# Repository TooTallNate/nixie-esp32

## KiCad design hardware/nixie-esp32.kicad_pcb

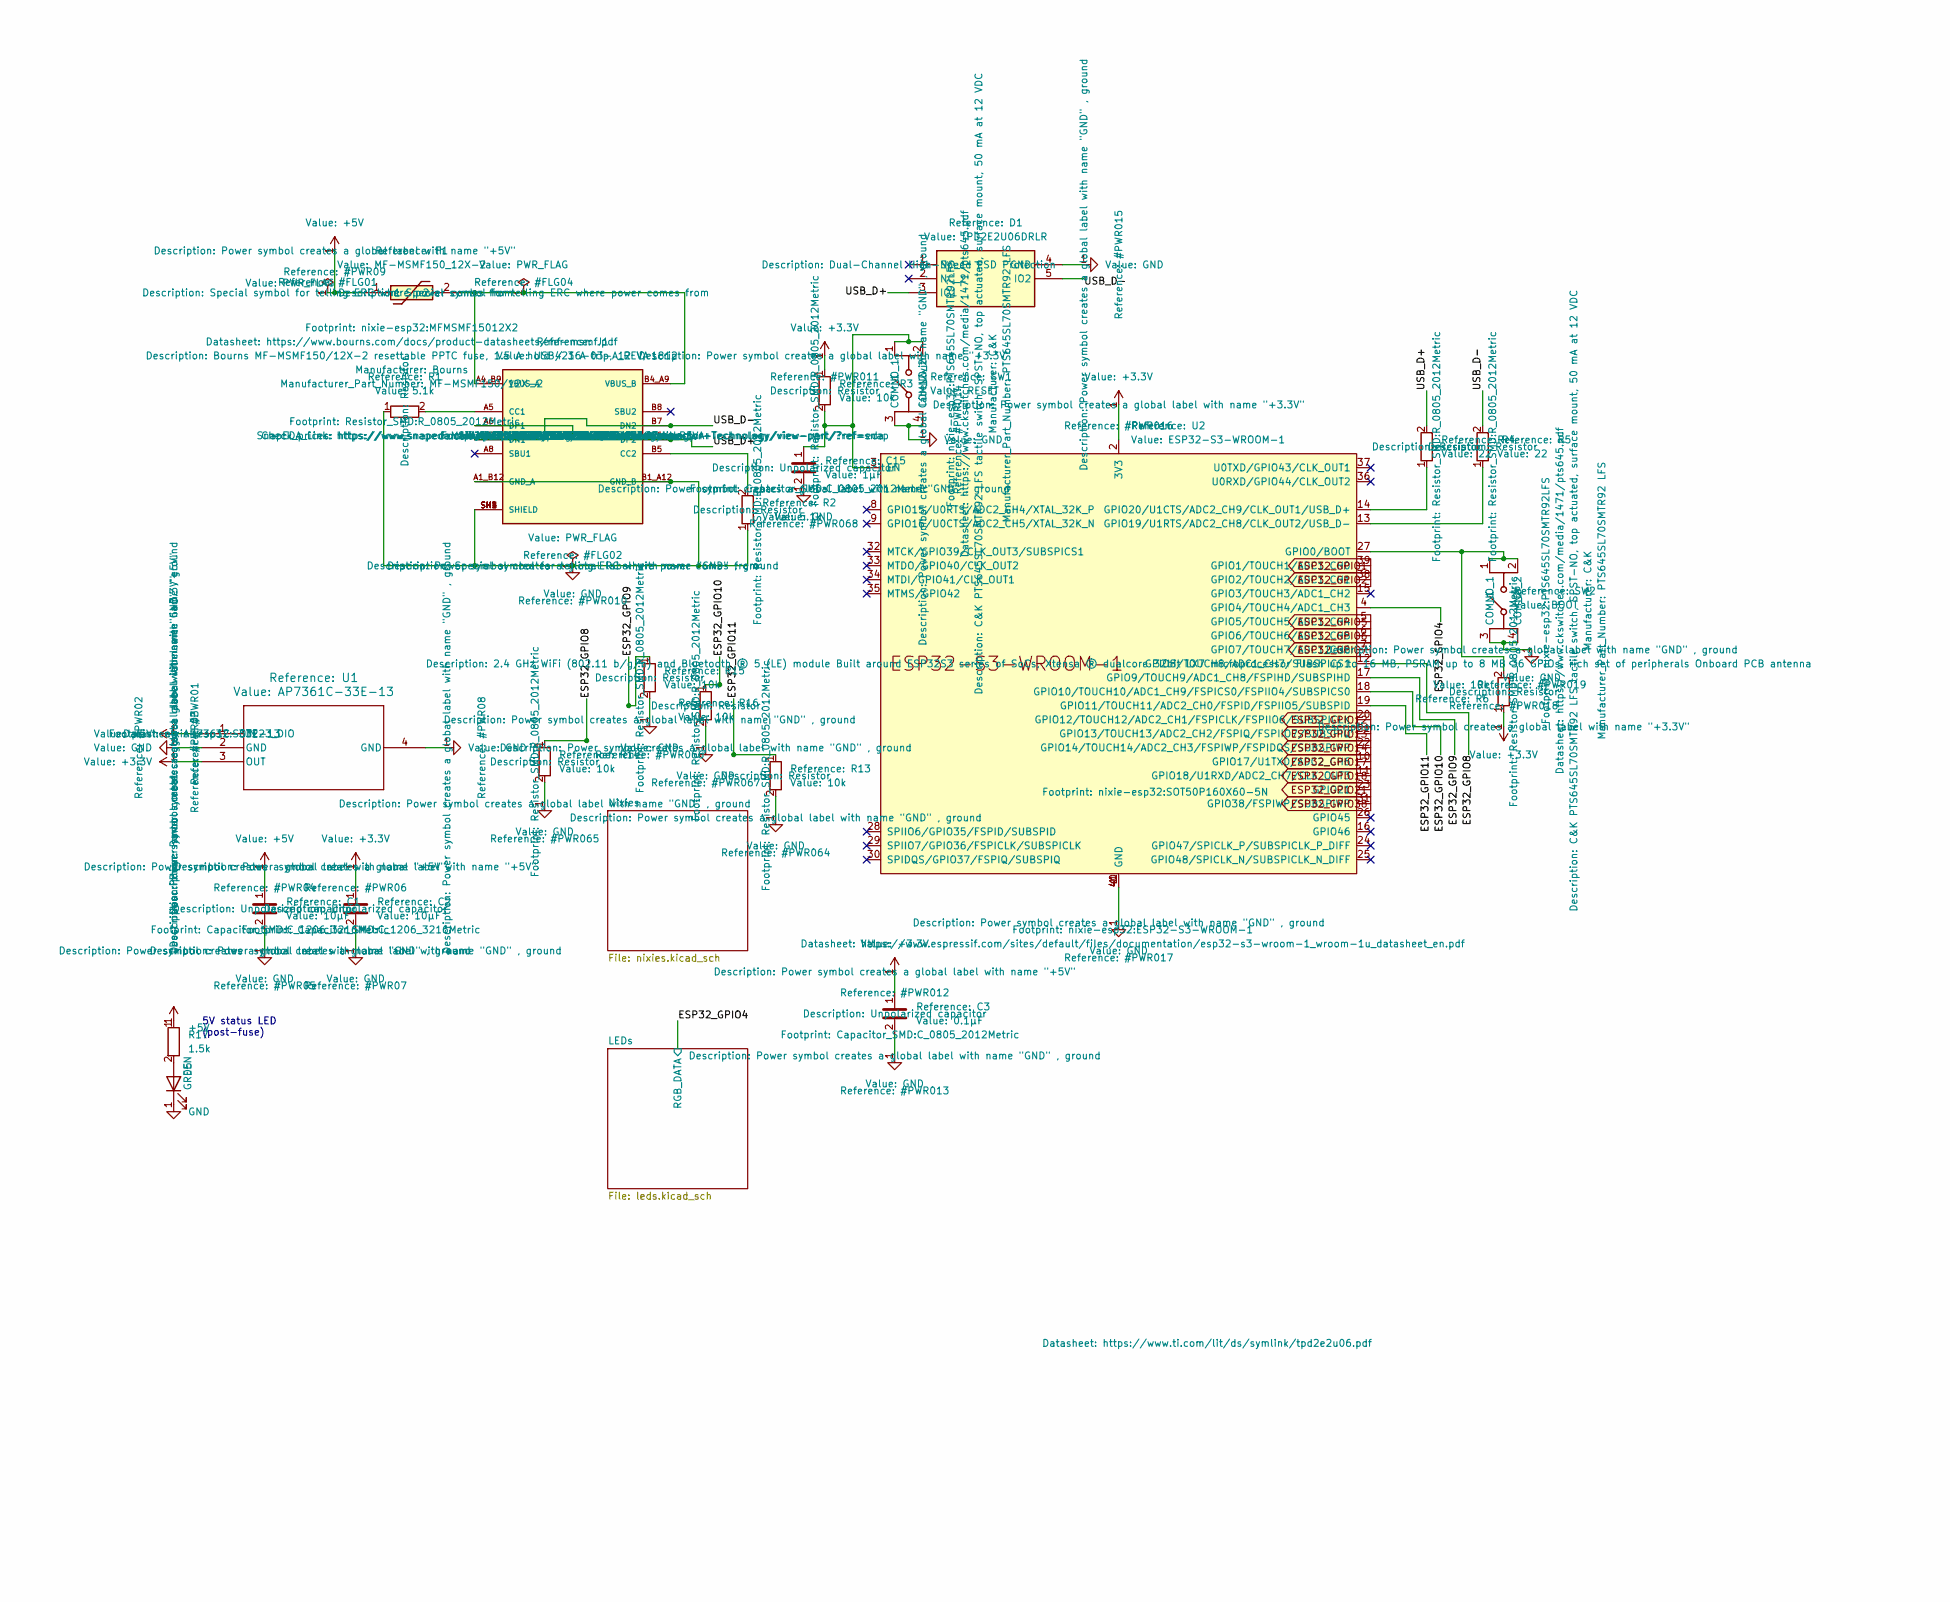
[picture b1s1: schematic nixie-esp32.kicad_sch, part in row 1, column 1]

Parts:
C1, C2: 10µF; C_1206_3216Metric
C3: 0.1µF; C_0805_2012Metric
C15: 1µF; C_0805_2012Metric
D1: TPD2E2U06DRLR; SOT50P160X60-5N; Mouser Part Number 595-TPD2E2U06DRLR
D5: GREEN; LED_0805_2012Metric
F1: MF-MSMF150_12X-2; MFMSMF15012X2; Manufacturer_Part_Number MF-MSMF150/12X-2
J1: USB4216-03-A_REVA; GCT_USB4216-03-A_REVA; PARTREV A
R1, R2: 5.1k; R_0805_2012Metric
R3, R6, R13, R14, R15, R16: 10k; R_0805_2012Metric
R4, R5: 22; R_0805_2012Metric
R17: 1.5k; R_0805_2012Metric
SW1: RESET; PTS645SL70SMTR92LFS; Manufacturer_Part_Number PTS645SL70SMTR92 LFS
SW2: BOOT; PTS645SL70SMTR92LFS; Manufacturer_Part_Number PTS645SL70SMTR92 LFS
U1: AP7361C-33E-13; SOT223_DIO
U2: ESP32-S3-WROOM-1

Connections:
+3.3V: C2.1, C3.1, R3.1, R6.1, U1.3 (OUT), U2.2 (3V3); also elsewhere on the board
+5V: C1.1, F1.1, R17.1, U1.1 (IN); also elsewhere on the board
/ESP32_GPIO4: U2.4 (GPIO4/TOUCH4/ADC1_CH3); also elsewhere on the board
/ESP32_GPIO8: R14.1, U2.12 (GPIO8/TOUCH8/ADC1_CH7/SUBSPICS1)
/ESP32_GPIO9: R15.1, U2.17 (GPIO9/TOUCH9/ADC1_CH8/FSPIHD/SUBSPIHD)
/ESP32_GPIO10: R16.1, U2.18 (GPIO10/TOUCH10/ADC1_CH9/FSPICS0/FSPIIO4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)
/ESP32_GPIO11: R13.1, U2.19 (GPIO11/TOUCH11/ADC2_CH0/FSPID/FSPIIO5/S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)
/USB_D+: D1.3 (IO1), J1.A6 (DP1), J1.B6 (DP2), R4.2
/USB_D-: D1.5 (IO2), J1.A7 (DN1), J1.B7 (DN2), R5.2
ESP32_GPIO1: U2.39 (GPIO1/TOUCH1/ADC1_CH0); also elsewhere on the board
ESP32_GPIO2: U2.38 (GPIO2/TOUCH2/ADC1_CH1); also elsewhere on the board
ESP32_GPIO5: U2.5 (GPIO5/TOUCH5/ADC1_CH4); also elsewhere on the board
ESP32_GPIO6: U2.6 (GPIO6/TOUCH6/ADC1_CH5); also elsewhere on the board
ESP32_GPIO7: U2.7 (GPIO7/TOUCH7/ADC1_CH6); also elsewhere on the board
ESP32_GPIO12: U2.20 (GPIO12/TOUCH12/ADC2_CH1/FSPICLK/FSPIIO6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); also elsewhere on the board
ESP32_GPIO13: U2.21 (GPIO13/TOUCH13/ADC2_CH2/FSPIQ/FSPIIO7/S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); also elsewhere on the board
ESP32_GPIO14: U2.22 (GPIO14/TOUCH14/ADC2_CH3/FSPIWP/FSPIDQS/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); also elsewhere on the board
ESP32_GPIO17: U2.10 (GPIO17/U1TXD/ADC2_CH6); also elsewhere on the board
ESP32_GPIO18: U2.11 (GPIO18/U1RXD/ADC2_CH7/CLK_OUT3); also elsewhere on the board
ESP32_GPIO21: U2.23 (GPIO21); also elsewhere on the board
ESP32_GPIO38: U2.31 (GPIO38/FSPIWP/SUBSPIWP); also elsewhere on the board
GND: C1.2, C2.2, C3.2, C15.2, D1.4 (GND), D5.1 (K), J1.A1_B12 (GND_A), J1.B1_A12 (GND_B), J1.SH1 (SHIELD), J1.SH2 (SHIELD), J1.SH3 (SHIELD), J1.SH4 (SHIELD), R1.1, R2.1, R13.2, R14.2, R15.2, R16.2, SW1.3 (COM_1), SW1.4 (COM_2), SW2.3 (COM_1), SW2.4 (COM_2), U1.2 (GND), U1.4 (GND), U2.1 (GND), U2.40 (GND), U2.41 (GND); also elsewhere on the board
unnamed: D5.2 (A), R17.2
unnamed: J1.A5 (CC1), R1.2
unnamed: J1.B5 (CC2), R2.2
unnamed: F1.2, J1.A4_B9 (VBUS_A), J1.B4_A9 (VBUS_B)
unnamed: C15.1, R3.2, SW1.1 (NO_1), SW1.2 (NO_2), U2.3 (EN)
unnamed: R6.2, SW2.1 (NO_1), SW2.2 (NO_2), U2.27 (GPIO0/BOOT)
unnamed: R5.1, U2.13 (GPIO19/U1RTS/ADC2_CH8/CLK_OUT2/USB_D-)
unnamed: R4.1, U2.14 (GPIO20/U1CTS/ADC2_CH9/CLK_OUT1/USB_D+)

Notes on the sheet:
5V status LED (post-fuse)

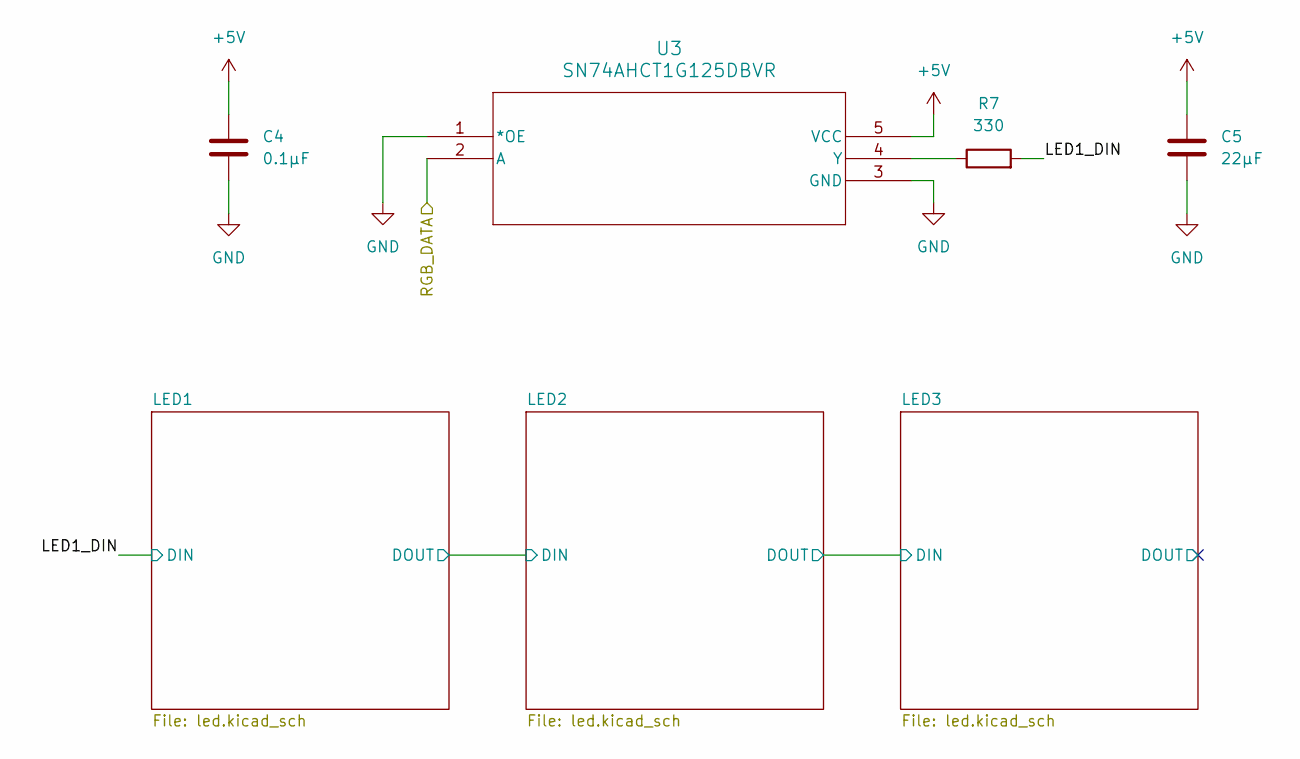
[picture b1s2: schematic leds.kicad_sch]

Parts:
C4: 0.1µF; C_0805_2012Metric
C5: 22µF; C_1206_3216Metric
R7: 330; R_0805_2012Metric
U3: SN74AHCT1G125DBVR; DBV5

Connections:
+5V: C4.1, C5.1, U3.5 (VCC); also elsewhere on the board
/ESP32_GPIO4: U3.2 (A); also elsewhere on the board
/LEDs/LED1_DIN: R7.2; also elsewhere on the board
GND: C4.2, C5.2, U3.1 (*OE), U3.3 (GND); also elsewhere on the board
unnamed: R7.1, U3.4 (Y)

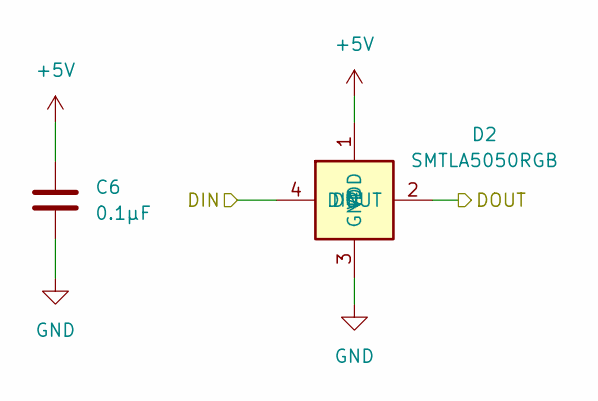
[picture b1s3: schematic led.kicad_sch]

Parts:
C6: 0.1µF; C_0805_2012Metric
D2: SMTLA5050RGB; Manufacturer_Part_Number SMTLA5050RGB

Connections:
+5V: C6.1, D2.1 (VDD); also elsewhere on the board
/LEDs/LED1/DOUT: D2.2 (DOUT); also elsewhere on the board
/LEDs/LED1_DIN: D2.4 (DIN); also elsewhere on the board
GND: C6.2, D2.3 (GND); also elsewhere on the board

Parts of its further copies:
C7, C8: 0.1µF; C_0805_2012Metric
D3, D4: SMTLA5050RGB; Manufacturer_Part_Number SMTLA5050RGB

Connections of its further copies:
+5V: C7.1, C8.1, D3.1 (VDD), D4.1 (VDD); also elsewhere on the board
/LEDs/LED1/DOUT: D3.4 (DIN); also elsewhere on the board
/LEDs/LED2/DOUT: D3.2 (DOUT), D4.4 (DIN)
/LEDs/LED3/DOUT: D4.2 (DOUT)
GND: C7.2, C8.2, D3.3 (GND), D4.3 (GND); also elsewhere on the board

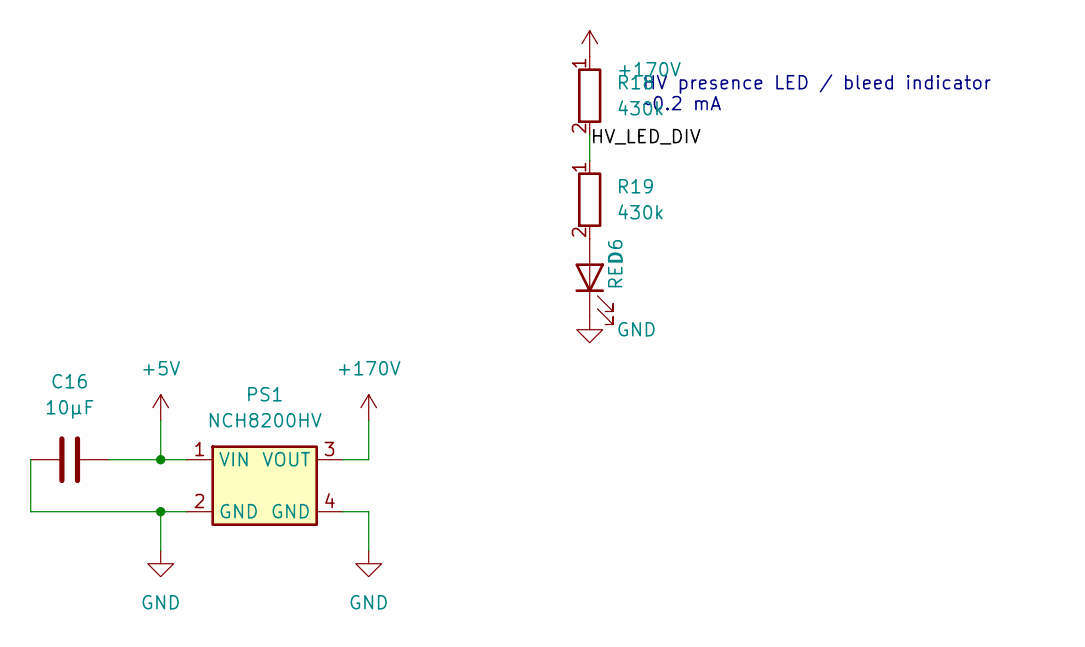
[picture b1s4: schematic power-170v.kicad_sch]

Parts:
C16: 10µF; C_1206_3216Metric
D6: RED; LED_0805_2012Metric
PS1: NCH8200HV
R18, R19: 430k; R_0805_2012Metric

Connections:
+5V: C16.1, PS1.1 (VIN); also elsewhere on the board
+170V: PS1.3 (VOUT), R18.1; also elsewhere on the board
/Nixies/Power170v/HV_LED_DIV: R18.2, R19.1
GND: C16.2, D6.1 (K), PS1.2 (GND), PS1.4 (GND); also elsewhere on the board
unnamed: D6.2 (A), R19.2

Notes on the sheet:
HV presence LED / bleed indicator ~0.2 mA

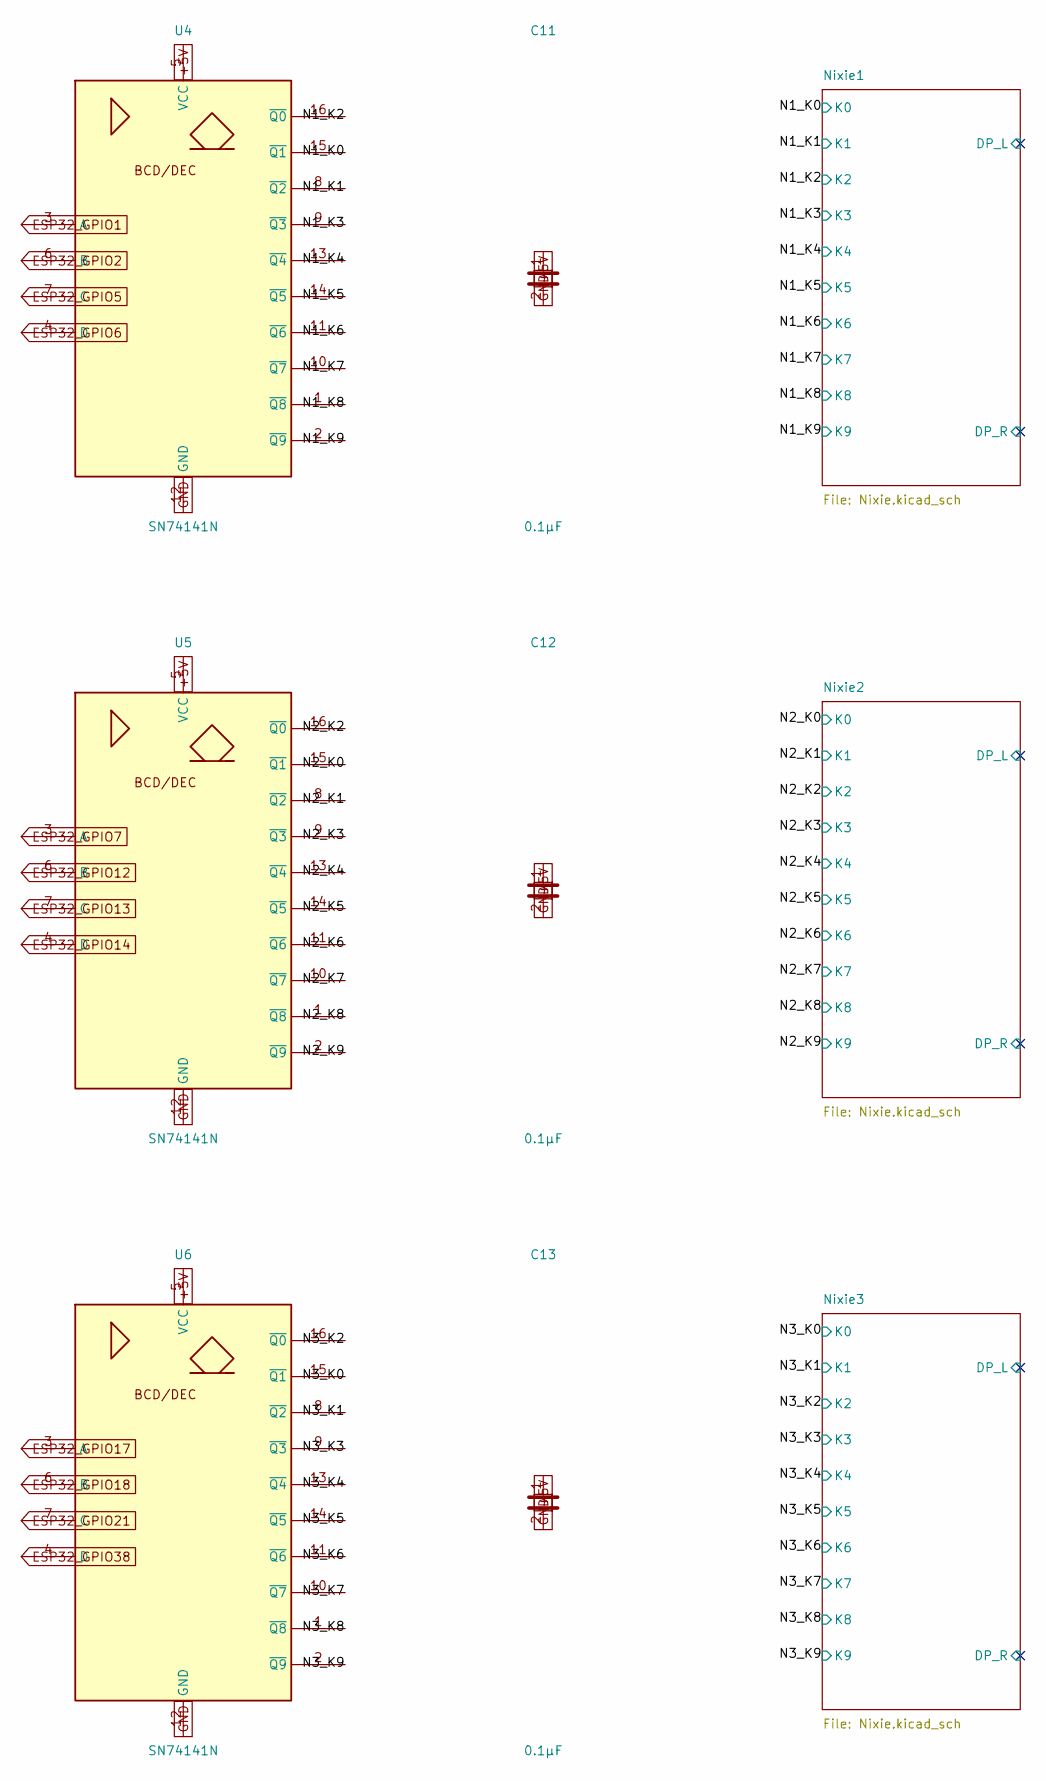
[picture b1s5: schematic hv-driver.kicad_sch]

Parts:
C11, C12, C13: 0.1µF; C_0805_2012Metric
U4, U5, U6: SN74141N; DIP-16_W7.62mm

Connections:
+5V: C11.1, C12.1, C13.1, U4.5 (VCC), U5.5 (VCC), U6.5 (VCC); also elsewhere on the board
/Nixies/HvDriver/N1_K0: U4.15 (~Q1); also elsewhere on the board
/Nixies/HvDriver/N1_K1: U4.8 (~Q2); also elsewhere on the board
/Nixies/HvDriver/N1_K2: U4.16 (~Q0); also elsewhere on the board
/Nixies/HvDriver/N1_K3: U4.9 (~Q3); also elsewhere on the board
/Nixies/HvDriver/N1_K4: U4.13 (~Q4); also elsewhere on the board
/Nixies/HvDriver/N1_K5: U4.14 (~Q5); also elsewhere on the board
/Nixies/HvDriver/N1_K6: U4.11 (~Q6); also elsewhere on the board
/Nixies/HvDriver/N1_K7: U4.10 (~Q7); also elsewhere on the board
/Nixies/HvDriver/N1_K8: U4.1 (~Q8); also elsewhere on the board
/Nixies/HvDriver/N1_K9: U4.2 (~Q9); also elsewhere on the board
/Nixies/HvDriver/N2_K0: U5.15 (~Q1); also elsewhere on the board
/Nixies/HvDriver/N2_K1: U5.8 (~Q2); also elsewhere on the board
/Nixies/HvDriver/N2_K2: U5.16 (~Q0); also elsewhere on the board
/Nixies/HvDriver/N2_K3: U5.9 (~Q3); also elsewhere on the board
/Nixies/HvDriver/N2_K4: U5.13 (~Q4); also elsewhere on the board
/Nixies/HvDriver/N2_K5: U5.14 (~Q5); also elsewhere on the board
/Nixies/HvDriver/N2_K6: U5.11 (~Q6); also elsewhere on the board
/Nixies/HvDriver/N2_K7: U5.10 (~Q7); also elsewhere on the board
/Nixies/HvDriver/N2_K8: U5.1 (~Q8); also elsewhere on the board
/Nixies/HvDriver/N2_K9: U5.2 (~Q9); also elsewhere on the board
/Nixies/HvDriver/N3_K0: U6.15 (~Q1); also elsewhere on the board
/Nixies/HvDriver/N3_K1: U6.8 (~Q2); also elsewhere on the board
/Nixies/HvDriver/N3_K2: U6.16 (~Q0); also elsewhere on the board
/Nixies/HvDriver/N3_K3: U6.9 (~Q3); also elsewhere on the board
/Nixies/HvDriver/N3_K4: U6.13 (~Q4); also elsewhere on the board
/Nixies/HvDriver/N3_K5: U6.14 (~Q5); also elsewhere on the board
/Nixies/HvDriver/N3_K6: U6.11 (~Q6); also elsewhere on the board
/Nixies/HvDriver/N3_K7: U6.10 (~Q7); also elsewhere on the board
/Nixies/HvDriver/N3_K8: U6.1 (~Q8); also elsewhere on the board
/Nixies/HvDriver/N3_K9: U6.2 (~Q9); also elsewhere on the board
ESP32_GPIO1: U4.3 (A); also elsewhere on the board
ESP32_GPIO2: U4.6 (B); also elsewhere on the board
ESP32_GPIO5: U4.7 (C); also elsewhere on the board
ESP32_GPIO6: U4.4 (D); also elsewhere on the board
ESP32_GPIO7: U5.3 (A); also elsewhere on the board
ESP32_GPIO12: U5.6 (B); also elsewhere on the board
ESP32_GPIO13: U5.7 (C); also elsewhere on the board
ESP32_GPIO14: U5.4 (D); also elsewhere on the board
ESP32_GPIO17: U6.3 (A); also elsewhere on the board
ESP32_GPIO18: U6.6 (B); also elsewhere on the board
ESP32_GPIO21: U6.7 (C); also elsewhere on the board
ESP32_GPIO38: U6.4 (D); also elsewhere on the board
GND: C11.2, C12.2, C13.2, U4.12 (GND), U5.12 (GND), U6.12 (GND); also elsewhere on the board

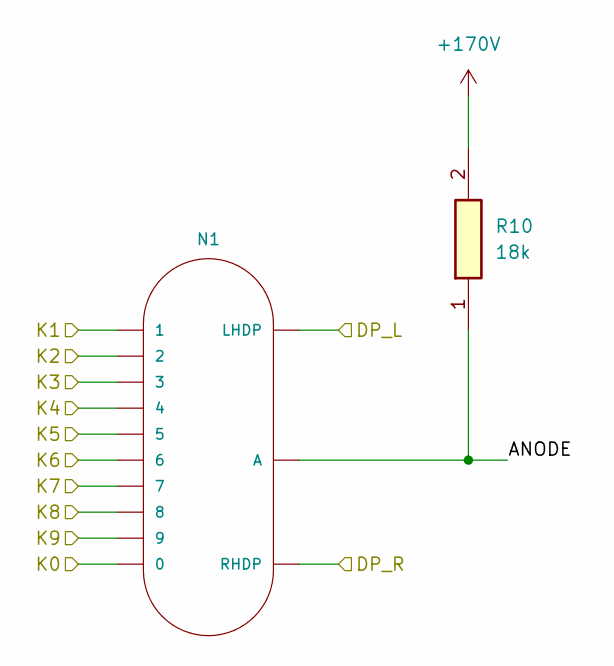
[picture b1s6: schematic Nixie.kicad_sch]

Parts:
N1: IN-14; nixies-us-IN-14
R10: 18k; RESC3116X65N; Tolerance 1%; Voltage_Rating 200 V; Manufacturer_Part_Number CRGH1206F18K

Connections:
+170V: R10.2; also elsewhere on the board
/Nixies/HvDriver/N1_K0: N1.0; also elsewhere on the board
/Nixies/HvDriver/N1_K1: N1.1; also elsewhere on the board
/Nixies/HvDriver/N1_K2: N1.2; also elsewhere on the board
/Nixies/HvDriver/N1_K3: N1.3; also elsewhere on the board
/Nixies/HvDriver/N1_K4: N1.4; also elsewhere on the board
/Nixies/HvDriver/N1_K5: N1.5; also elsewhere on the board
/Nixies/HvDriver/N1_K6: N1.6; also elsewhere on the board
/Nixies/HvDriver/N1_K7: N1.7; also elsewhere on the board
/Nixies/HvDriver/N1_K8: N1.8; also elsewhere on the board
/Nixies/HvDriver/N1_K9: N1.9; also elsewhere on the board
/Nixies/HvDriver/Nixie1/ANODE: N1.A, R10.1

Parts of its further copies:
N2, N3: IN-14; nixies-us-IN-14
R11, R12: 18k; RESC3116X65N; Tolerance 1%; Voltage_Rating 200 V; Manufacturer_Part_Number CRGH1206F18K

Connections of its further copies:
+170V: R11.2, R12.2; also elsewhere on the board
/Nixies/HvDriver/N2_K0: N2.0; also elsewhere on the board
/Nixies/HvDriver/N2_K1: N2.1; also elsewhere on the board
/Nixies/HvDriver/N2_K2: N2.2; also elsewhere on the board
/Nixies/HvDriver/N2_K3: N2.3; also elsewhere on the board
/Nixies/HvDriver/N2_K4: N2.4; also elsewhere on the board
/Nixies/HvDriver/N2_K5: N2.5; also elsewhere on the board
/Nixies/HvDriver/N2_K6: N2.6; also elsewhere on the board
/Nixies/HvDriver/N2_K7: N2.7; also elsewhere on the board
/Nixies/HvDriver/N2_K8: N2.8; also elsewhere on the board
/Nixies/HvDriver/N2_K9: N2.9; also elsewhere on the board
/Nixies/HvDriver/N3_K0: N3.0; also elsewhere on the board
/Nixies/HvDriver/N3_K1: N3.1; also elsewhere on the board
/Nixies/HvDriver/N3_K2: N3.2; also elsewhere on the board
/Nixies/HvDriver/N3_K3: N3.3; also elsewhere on the board
/Nixies/HvDriver/N3_K4: N3.4; also elsewhere on the board
/Nixies/HvDriver/N3_K5: N3.5; also elsewhere on the board
/Nixies/HvDriver/N3_K6: N3.6; also elsewhere on the board
/Nixies/HvDriver/N3_K7: N3.7; also elsewhere on the board
/Nixies/HvDriver/N3_K8: N3.8; also elsewhere on the board
/Nixies/HvDriver/N3_K9: N3.9; also elsewhere on the board
/Nixies/HvDriver/Nixie2/ANODE: N2.A, R11.1
/Nixies/HvDriver/Nixie3/ANODE: N3.A, R12.1

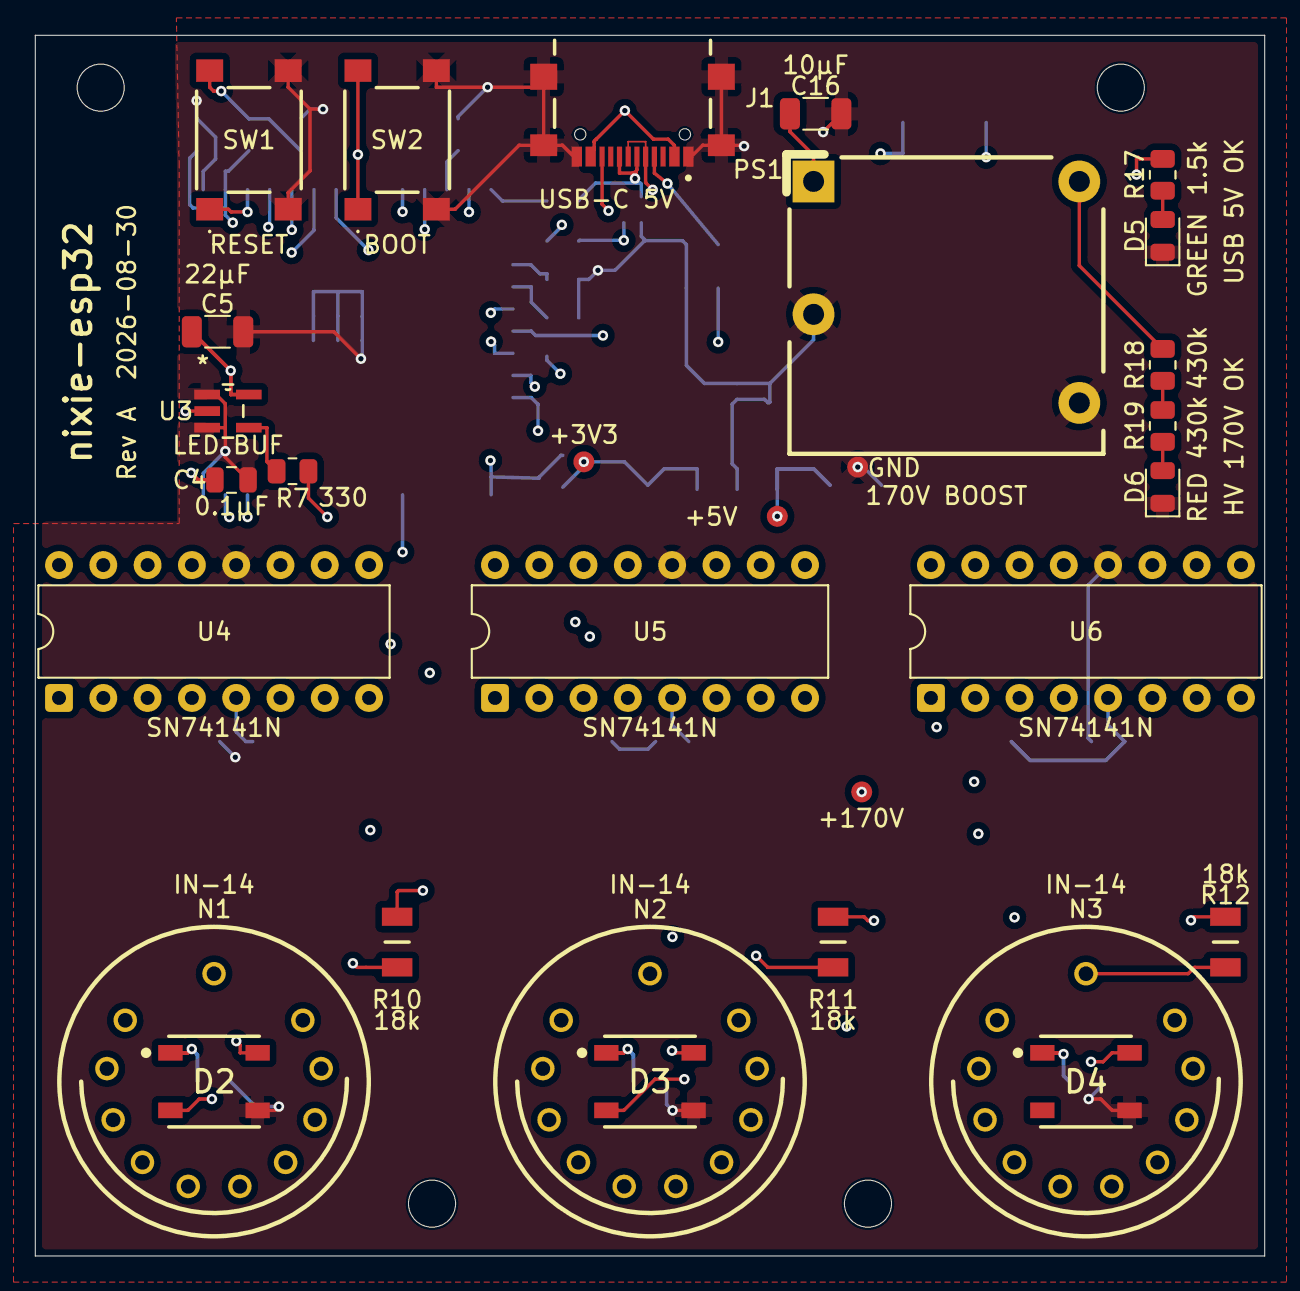
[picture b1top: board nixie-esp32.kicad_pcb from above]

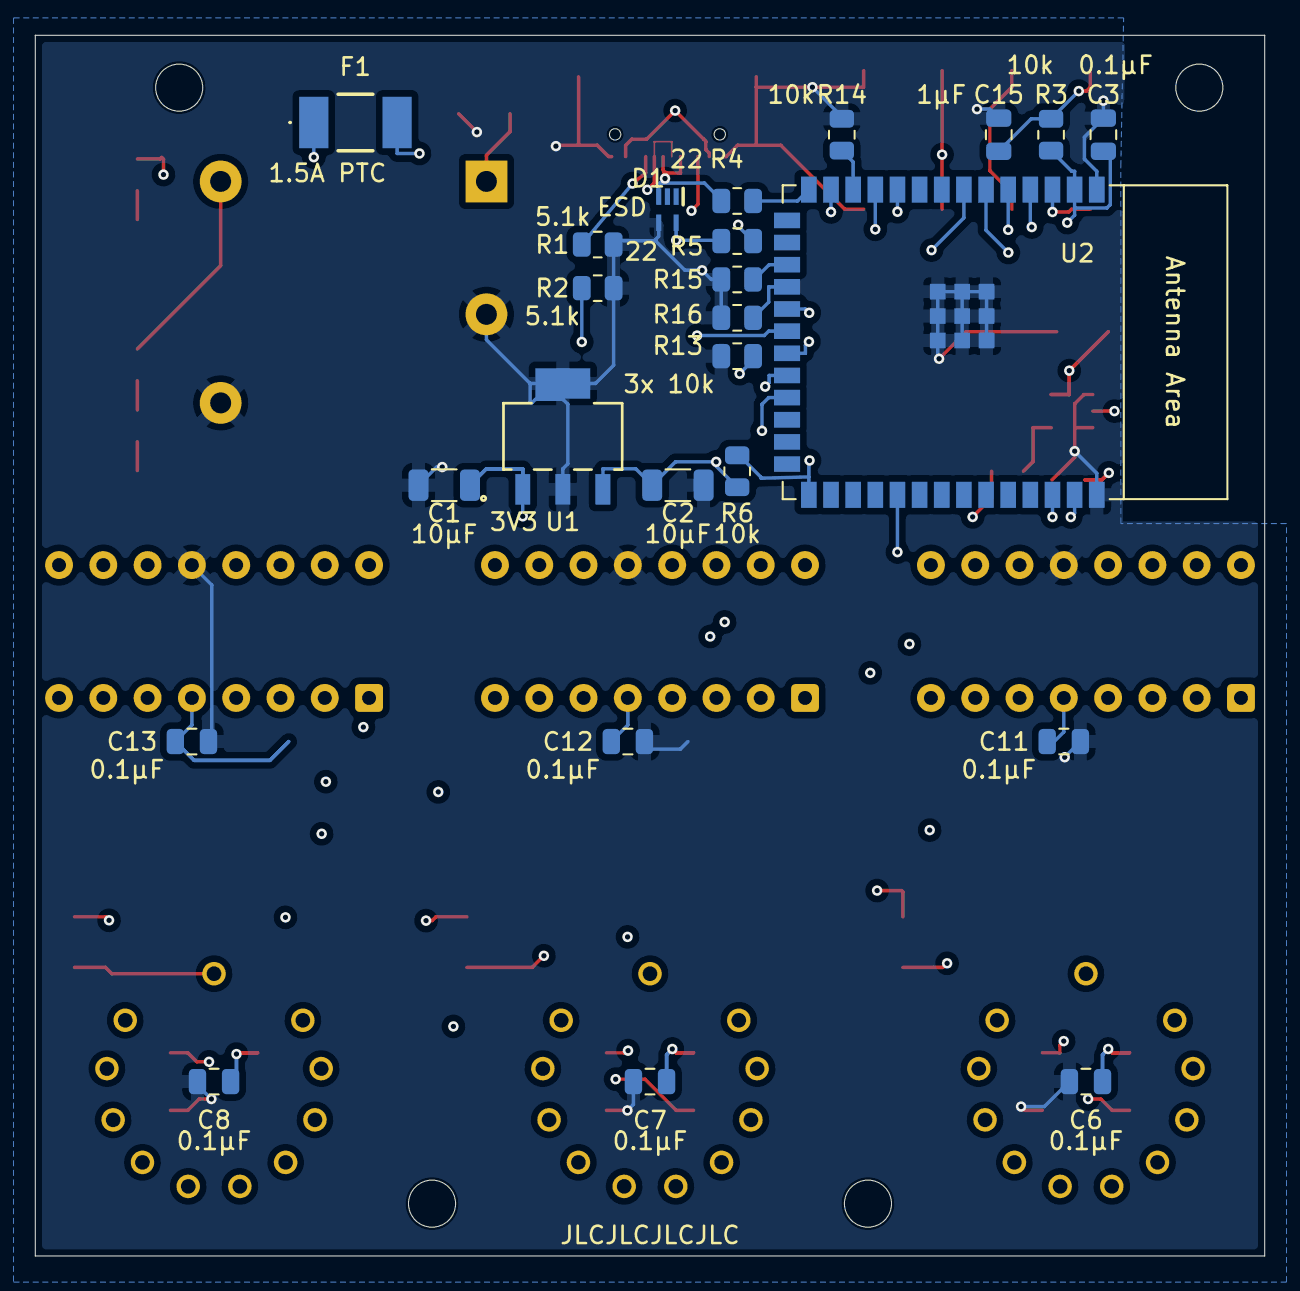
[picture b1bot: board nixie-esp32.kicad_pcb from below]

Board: 6 copper layers, 70.5 x 70.0 mm, 58 parts (24 on the bottom side), 70 nets.

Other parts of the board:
H1, H2, H3, H4: MountingHole_2.7mm_M2.5
TP1: GND
TP2: +3.3V
TP3: +5V
TP4: +170V

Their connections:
+3.3V: TP2.1; also elsewhere on the board
+5V: TP3.1; also elsewhere on the board
+170V: TP4.1; also elsewhere on the board
GND: TP1.1; also elsewhere on the board

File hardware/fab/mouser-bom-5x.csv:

Quantity,Mfr Part Number,Manufacturer,Description,Reference Designators,Per Board,Notes
100,CL21B104KBCNNNC,Samsung Electro-Mechanics,"CAP CER 0.1uF 50V X7R 0805","C3 C4 C6 C7 C8 C11 C12 C13",8,decoupling
25,CL21B105KAFNNNE,Samsung Electro-Mechanics,"CAP CER 1uF 25V X7R 0805",C15,1,
25,CL31A106KAHNNNE,Samsung Electro-Mechanics,"CAP CER 10uF 25V X5R 1206","C1 C2 C16",3,rail bulk
25,CL31A226KAHNNNE,Samsung Electro-Mechanics,"CAP CER 22uF 25V X5R 1206",C5,1,ESP32 bulk
25,RC0805FR-0722RL,YAGEO,"RES 22 OHM 1% 1/8W 0805","R4 R5",2,USB series
25,RC0805FR-07330RL,YAGEO,"RES 330 OHM 1% 1/8W 0805",R7,1,LED data series
25,RC0805FR-071K5L,YAGEO,"RES 1.5K OHM 1% 1/8W 0805",R17,1,5V status LED
25,RC0805FR-075K1L,YAGEO,"RES 5.1K OHM 1% 1/8W 0805","R1 R2",2,USB-C CC pulldowns
100,RC0805FR-0710KL,YAGEO,"RES 10K OHM 1% 1/8W 0805","R3 R6 R13 R14 R15 R16",6,
25,CRGH1206F18K,TE Connectivity,"RES 18K OHM 1% 1/2W 1206 200V","R10 R11 R12",3,nixie anode - keep 1206 200V part
25,RC0805FR-07430KL,YAGEO,"RES 430K OHM 1% 1/8W 0805","R18 R19",2,HV status LED divider
10,LTST-C170GKT,Lite-On,"LED GREEN 0805",D5,1,5V status
10,APT2012SURCK,Kingbright,"LED SUPER RED 0805",D6,1,HV status - high brightness for 0.2mA drive
20,SMTLA5050RGB,Bivar,"LED RGB ADDRESSABLE 5050","D2 D3 D4",3,tube backlight
8,TPD2E2U06DRLR,Texas Instruments,"TVS DIODE USB ESD SOT-553",D1,1,
8,AP7361C-33E-13,Diodes Incorporated,"IC REG LDO 3.3V 1A SOT-223",U1,1,
8,SN74AHCT1G125DBVR,Texas Instruments,"IC BUF NON-INVERT 5.5V SOT-23-5",U3,1,LED level shifter
6,ESP32-S3-WROOM-1-N8,Espressif Systems,"WIFI/BT MODULE ESP32-S3 8MB",U2,1,VERIFY FLASH VARIANT - N8 assumed
8,USB4216-03-A,GCT,"CONN RCPT USB2.0 TYPE-C 16P",J1,1,
10,MF-MSMF150/12X-2,Bourns,"PTC RESET FUSE 12V 1.5A 1812",F1,1,
15,PTS645SL70SMTR92 LFS,C&K,"SWITCH TACTILE SPST-NO SMD","SW1 SW2",2,RESET/BOOT
18,ED16DT,On Shore Technology,"SOCKET IC DIP-16 7.62MM",U4 U5 U6 (optional),3,recommended for vintage 74141/K155ID1
